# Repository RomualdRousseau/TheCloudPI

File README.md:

# TheCloudPI
Clusters of PI running docker swarm

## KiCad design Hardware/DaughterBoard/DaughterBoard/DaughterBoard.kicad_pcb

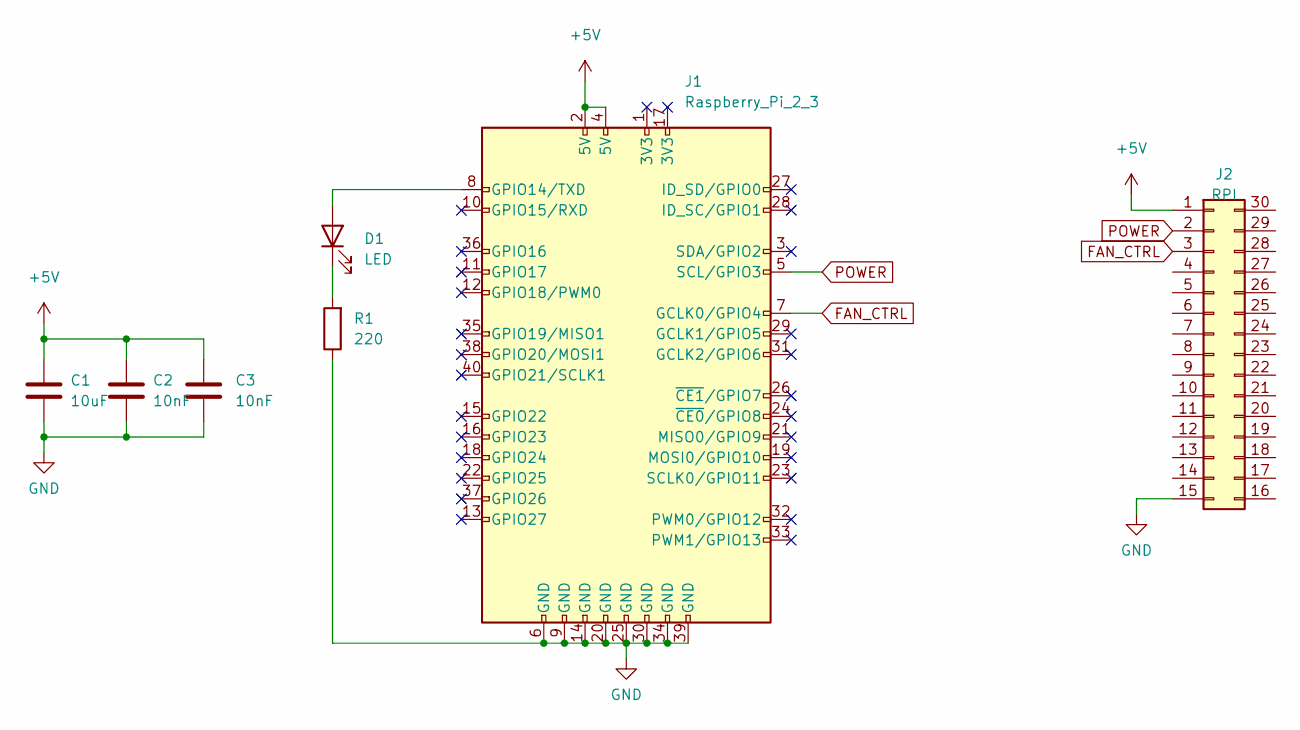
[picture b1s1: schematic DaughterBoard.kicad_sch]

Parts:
C1: 10uF; C_0805_2012Metric_Pad1.18x1.45mm_HandSolder
C2, C3: 10nF; C_0603_1608Metric_Pad1.08x0.95mm_HandSolder
D1: LED; LED_0603_1608Metric_Pad1.05x0.95mm_HandSolder
J1: Raspberry_Pi_2_3; PinSocket_2x20_P2.54mm_Vertical
J2: RPI; NES_PCBEdge
R1: 220; R_0603_1608Metric_Pad0.98x0.95mm_HandSolder

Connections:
+5V: C1.1, C2.1, C3.1, J1.2 (5V), J1.4 (5V), J2.1
FAN_CTRL: J1.7 (GCLK0/GPIO4), J2.3
GND: C1.2, C2.2, C3.2, J1.6 (GND), J1.9 (GND), J1.14 (GND), J1.20 (GND), J1.25 (GND), J1.30 (GND), J1.34 (GND), J1.39 (GND), J2.15, R1.1
unnamed: D1.1 (K), R1.2
unnamed: D1.2 (A), J1.8 (GPIO14/TXD)
POWER: J1.5 (SCL/GPIO3), J2.2

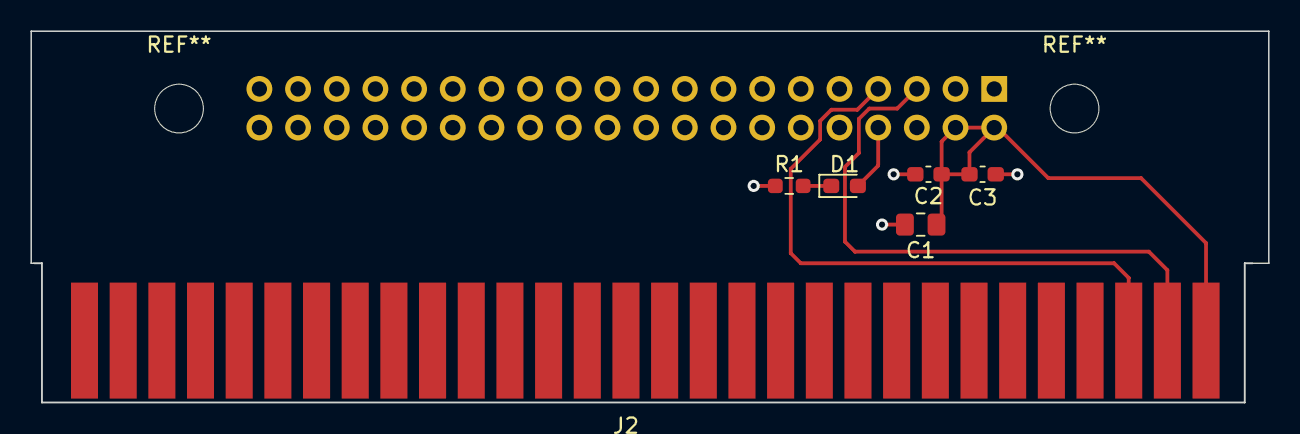
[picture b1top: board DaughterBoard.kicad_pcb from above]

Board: 2 copper layers, 81.3 x 24.4 mm, 7 parts (1 on the bottom side), 6 nets.

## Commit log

2022-11-01 New motherboard
2025-11-04 feat: modify mother board
